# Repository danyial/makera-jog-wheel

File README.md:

# Makera jog wheel

A battery-powered Wi-Fi handwheel (MPG, manual pulse generator) for the **Makera Z1 Pro** desktop CNC mill. An ESP32 (DFRobot **FireBeetle 2 ESP32-UE**) with a 100-pulse handwheel, four axis buttons and a 1.3″ OLED connects directly to the machine over Wi-Fi and jogs X, Y, Z and optionally the rotary axis A. No PC needed, and it works alongside Makera Studio.

> **Safety first. Read the [safety notice](#safety) before you connect this to a machine.**

The firmware's user-facing texts (display, web UI, serial output) are in German; all documentation is in English.

## Features

- **Jog gate.** The machine only moves when an axis is selected, a fresh machine status is available and the machine is ready. A running job, an alarm, a stale status or lost Wi-Fi lock the wheel; motion by another client ends the jog session ([SPEC 8.5](SPEC.md), [8.7](SPEC.md)).
- **Bounded overrun.** Commands are planned inside a small window ahead of the machine position. When the wheel stops, the machine stops after at most that window (5 mm X/Y, 1 mm Z, 2° A); surplus detents are dropped, never queued ([SPEC 8.7](SPEC.md)).
- **Speed-dependent step size.** Slow turning moves 0.01 mm per detent, faster turning 0.05 and 0.1 mm, no range switch. The feed rate follows the turning speed and is capped by the machine's own maximum rates, read at runtime ([SPEC 8.6](SPEC.md)).
- **Axis selection** with lit buttons, auto-deselect after inactivity, and an optional rotary axis A.
- **Unlock after an alarm** by holding an axis button for 5 s (sends `$X`, like the unlock dialog in Makera Studio). Nothing moves afterwards without new turning ([SPEC 8.10](SPEC.md)).
- **Setup portal.** First start (or X held at power-on) opens an access point with a captive portal for Wi-Fi credentials, machine IP and options. No code changes needed.
- **Web UI** in normal operation (`http://handrad.local/`): read-only status page with machine state, position and battery, a 2D position map of the spoilboard and a 3D view (three.js, served from the handwheel's flash, no internet needed); password-protected settings page.
- **OTA updates** over Wi-Fi (espota), opt-in, password-protected, refused while an axis is selected or the battery is low ([SPEC 9.5](SPEC.md)).
- **Soft power.** The on/off button is an input; off means deep sleep, so the battery keeps charging over USB-C while the handwheel is off ([SPEC 9.3](SPEC.md)).
- **Battery monitoring**, low-battery warning and an orderly shutdown when empty; screensaver against OLED burn-in.
- **Tested core logic.** Everything that decides about motion lives in `lib/core` (plain C++17, no Arduino) and is covered by Unity tests that run on the host.

## Hardware

- **Bill of materials:** [`hardware/BOM.md`](hardware/BOM.md) (FireBeetle 2 ESP32-UE, ZSS600 handwheel, SH1106 OLED, 12 mm LED push buttons, 1S LiPo, u.FL antenna, connectors, screws).
- **Carrier board:** single-sided, millable 78 × 66 mm board, generated with KiCad's Python API. Gerber, drill and SVG/PDF files: [`hardware/README.md`](hardware/README.md), [`hardware/handrad_pcb/fab/`](hardware/handrad_pcb/fab/).
- **Enclosure:** printable two-part handheld enclosure (92 × 200 × 40 mm), STL and STEP: [`hardware/enclosure/README.md`](hardware/enclosure/README.md).
- **Wiring and pin map:** [`WIRING.md`](WIRING.md), GPIOs in [`include/pins.h`](include/pins.h).
- **Bring-up checks:** [`HARDWARE_CHECKLIST.md`](HARDWARE_CHECKLIST.md) lists everything that can only be verified on real hardware. Work through it before trusting the handwheel with a machine.

## Build and flash

Requires [PlatformIO](https://platformio.org/).

```bash
pio test -e native                 # unit tests of the core logic on the host
pio run -e firebeetle              # build the firmware
pio run -e firebeetle -t upload    # flash over USB
pio device monitor                 # serial console, 115200 baud
```

Over Wi-Fi, once "Update über WLAN erlauben" (allow update over Wi-Fi) is enabled in the settings and no axis is selected; the password is the handwheel password shown during setup:

```bash
HANDRAD_OTA_PASS=<handwheel password> pio run -e firebeetle-ota -t upload
```

The generated web assets (`src/web_assets.h`) are rebuilt with `python3 -I tools/make_web_assets.py`. Setup, the portal and all screens are described in [`SPEC.md`](SPEC.md) chapters 9 and 10.

## Documentation

- [`SPEC.md`](SPEC.md): the full specification (architecture, machine protocol, jog logic, constants, tests, acceptance criteria).
- [`DECISIONS.md`](DECISIONS.md): every design decision with question, decision and rationale, including the accepted residual risks.
- [`WIRING.md`](WIRING.md): netlist, connectors, safety notes.
- [`HARDWARE_CHECKLIST.md`](HARDWARE_CHECKLIST.md): manual hardware checks.

Some documents mention files that exist only in the author's private working copy (third-party CAD models, the Makera logo). They are not part of this repository; the firmware, board and enclosure build without them.

## Safety

This is a hobby project, provided **as is, without any warranty** (see [`LICENSE`](LICENSE)). It moves a real machine with a spinning tool.

- The handwheel **can move the machine**. A firmware bug, a hardware fault, a wrong pin map or a misread status can cause unexpected motion. Within the documented limits the machine may also keep moving for a short distance after the wheel stops.
- It is **not an emergency stop** and not a safety device. Keep the machine's own emergency stop within reach at all times.
- Test carefully: work through [`HARDWARE_CHECKLIST.md`](HARDWARE_CHECKLIST.md), start without a tool and with the spindle off, at a safe height, with small steps, and read the residual risks in [`DECISIONS.md`](DECISIONS.md) and [`WIRING.md`](WIRING.md).
- You use it at your own risk and are responsible for your machine, your workpiece and yourself.

## Trademarks

Makera and Carvera are trademarks of Makera Inc. This project is not affiliated with, endorsed by or sponsored by Makera; the names are used only to describe which machine the handwheel works with. The Makera logo is not included (the screensaver and the enclosure engraving show a neutral "MPG").

The spoilboard and rotary-axis dimensions in `include/spoilboard_geometry.h` and `include/a_axis_geometry.h` were derived (simplified hole positions and bounding boxes) from Makera's public CAD files at [github.com/MakeraInc/CarveraProfiles](https://github.com/MakeraInc/CarveraProfiles). The CAD files themselves are not included; `tools/make_spoilboard_geometry.py` and `tools/make_a_axis_geometry.py` regenerate the headers from your own download.

## Licence and third-party components

This project is licensed under the [MIT licence](LICENSE).

Third-party components:

- **three.js** 0.160.0 and its `OrbitControls` (`web/vendor/`, embedded gzipped in `src/web_assets.h`): MIT licence, © three.js authors, see [`web/vendor/three-LICENSE`](web/vendor/three-LICENSE).
- **KiCad libraries:** the board file contains footprints from the KiCad standard libraries and references their 3D models (not included); the board renders in `hardware/handrad_pcb/fab/` show those models. The KiCad libraries are licensed under CC BY-SA 4.0 with an exception for designs and generated files that use them ([kicad.org/libraries/license](https://www.kicad.org/libraries/license/)).
- Fetched at build time by PlatformIO, not included: **U8g2** (BSD 2-clause), **Arduino-ESP32** and **ESP-IDF** (LGPL 2.1 / Apache 2.0), **Unity** test framework (MIT).

The simplified FireBeetle and pogo-pin models in `hardware/models/` are generated by `hardware/models/make_models.py` and are part of this project.

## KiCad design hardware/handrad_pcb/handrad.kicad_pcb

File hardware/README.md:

# Carrier board (tickets #20, #25, #49)

The enclosure (ticket #30) is described in [`enclosure/README.md`](enclosure/README.md). The full bill of materials is in [`BOM.md`](BOM.md).

Single-sided, millable board for the handwheel: FireBeetle 2 ESP32-UE in female headers, AO3401, 0805 resistors, JST-XH connectors. Rounded corners (r = 3 mm), **78 × 66 mm**, 4 × M3.

## Files

| File | Contents |
|---|---|
| `generate_board.py` | Generates the board via KiCad Python (`pcbnew`). Source of truth for parts, nets and tracks. |
| `export.sh` | Generates board, DRC report and fabrication data into `handrad_pcb/fab/`. |
| `handrad_pcb/handrad.kicad_pcb` | Board (open in KiCad 10). |
| `handrad_pcb/fab/handrad-B_Cu.gbr` | Copper layer (bottom), Gerber |
| `handrad_pcb/fab/handrad-Edge_Cuts.gbr` | Outline, Gerber: **one** closed polyline, corner arcs as a fine polygon. Generated by `outline_gerber.py`, because Makera Studio does not recognise the KiCad outline (separate segments with arcs) as a board outline. |
| `handrad_pcb/fab/handrad.drl` | Drill file, Excellon (mm): 1.0 mm for all pins, 0.8 mm for J1 (JST-PH) and the pogo pins, 3.2 mm mounting holes |
| `handrad_pcb/fab/handrad-B_Cu-mirrored.svg` | Copper side seen from below (mirrored), alternative to the Gerber |
| `handrad_pcb/fab/handrad-1to1.pdf` | 1:1 top view for the paper test |
| `handrad_pcb/fab/handrad.step` | 3D model of the assembly (board, FireBeetle, female headers, connectors, SMD, pogo pins) for CAD/enclosure. **Private repository only** (ticket #50): with `hardware/vendor/` present the file contains the licensed DFRobot model, which must not be redistributed, so the public export leaves it out. `export.sh` regenerates it on every run. |
| `handrad_pcb/fab/handrad-3d.png`, `handrad-3d-bottom.png` | Renderings |
| `handrad_pcb/fab/handrad-top.png` | Top view render with the connector labels (J-number, function, pin names) |
| `handrad_pcb/fab/handrad-top-labels.svg` | 2D top view: silkscreen over the copper (seen from above) and outline |
| `models/make_models.py` | Generates the simplified STEP models for the FireBeetle (`firebeetle2_esp32ue.step`) and the pogo pin P50-J1 (`pogo_p50_j1.step`) |

To change: adjust the parameters at the top of `generate_board.py` (e.g. `ROW`), then run `./hardware/export.sh`.

## Layout

- **Landscape (ticket #25):** The FireBeetle sits on top of the board rotated by 90°, the USB-C socket points left and protrudes 1.0 mm beyond the board edge. The former right pin row (VCC … D10, 14 pins) is now the top row, the former left one (RST … RX, 18 pins) the bottom row.
- **Connector rows (rev 2, ticket #49):** upper row (y = 43 mm): J4 display, J6 handwheel (left), J2 on/off button (right end, next to the button in the right enclosure wall). Lower row (y = 54 mm, next to the board edge towards the axis buttons): J9 X, J8 Y, J5 Z, J7 A from left to right, pin 1 at x = 22.0 / 35.5 / 49.0 / 62.5. Battery J1 sits directly above J2 at the right edge (pin 1 at x 66.0, y 31.5): battery and on/off cables both go to the right side of the enclosure, and the battery tracks just run further down the right edge. Left of J2 in the upper row is impossible (the lanes on the right come down there); in the rows the battery lines would have to cross those lanes. Why this way round: the buttons sit just below the board in the enclosure (shortest leads, same order X, Y, Z, A as the buttons); the display cable comes from above; the handwheel cable comes over the battery anyway and reaches the upper row past the button plugs.
- **Topology (crossing-free on one layer):**
  - Battery: `BAT−` (outer) and `BAT+` run from the pogo pins upwards, along the top edge to the right and down the right edge to J1 above J2. `BAT+` is not switched: the battery is always on the FireBeetle's "Li-ion" pads (soft power, SPEC 9.3). The on/off lane passes below J1 into J2.
  - 3V3 rail above the top row; the pull-ups R4/R5 stand vertically right above the pins of buttons Z/A (GPIO35/36, input only).
  - Display (top row pins 2–5) inwards, under the FireBeetle to the left and down the left edge, then right into J4 from above. Next to it on the inside, `ENC_PWR` runs from bottom row pin 6 under the FireBeetle to the left, past RST, and into R6/Q1 from the left.
  - Q1 sits mirrored on the bottom side; its pins there necessarily follow G, S, D clockwise. With D at the bottom, G is on the left and S on the right. That is why `ENC_PWR` must come from the left.
  - Handwheel J6 (0V, A, B, V+): A/B jog left from bottom pins 7/8 into J6 pins 2/3; `ENC_VCC` runs from Q1 below J6 to V+ (pin 4) with R1/R2 below pins 2/3; the wheel's 0V comes from FireBeetle bottom pin 4 (GND) from above (net `GND_ENC`).
  - Buttons X and Y: bottom pins 12/13 (X) and 15/16 (Y) straight down between J6 and J2, then left in the band between the rows into J9/J8 from above (the line from the leftmost pin runs highest).
  - Right group: top pins 6, 7, 10, 11, 12 fan out under the FireBeetle (rightmost pin highest) into lanes right of the rows, inner to outer: LED_Z, BTN_Z, BTN_A, LED_A, PWR_SW. LED_Z/BTN_Z drop into J5 with a 45° jog, BTN_A/LED_A turn right in the band into J7, PWR_SW (outermost) turns right above everything into J2.
  - GND: J4 GND straight down to the bus along the lower edge, the bus to J7 pin 4; J2's GND drops straight onto J7 pin 4; all other button GND pins join the bus from above. GND from the FireBeetle comes via top row pin 3 (display line), the wheel's via bottom pin 4.
- **Two 3V3 and two GND nets:** `+3V3` (top row pin 2: display, button pull-ups) and `+3V3_ENC` (bottom row pin 2: R6, source of Q1); `GND` (top row pin 3: display, buttons, on/off) and `GND_ENC` (bottom row pin 4: wheel 0V). On the FireBeetle they are the same rails. On one layer they cannot be joined without crossing the display lines. That is why they have separate names and the DRC reports no unconnected items.
- **Copper on the bottom only (B.Cu).** Female headers and JST-XH are inserted **from the top** and soldered underneath. The SMD parts (R1, R2, R4–R6, Q1) sit **underneath** on the copper side.
- Pads enlarged for an annular ring ≥ 0.4 mm (no plated through-holes when milling).
- Milling rules: tracks 0.8 mm (supply 1.0 mm), clearance ≥ 0.4 mm (between parallel tracks ≥ 0.5 mm). No vias, no jumpers. No 90° bends: every bend is made of two 45° chamfers (only T junctions stay right-angled).
- M3 mounting holes symmetric, 4.5 mm from each corner.
- The bottom side must be mirrored for milling. In Makera Studio, import the Gerber as bottom layer or use the mirrored SVG. Check the mirroring on a paper printout first.

## Parts

| Ref | Part | Nets |
|---|---|---|
| U1A / U1B | Female header 1×18 (bottom) / 1×14 (top), 2.54 mm (FireBeetle) | see `include/pins.h` |
| Q1 | AO3401 (SOT-23), above J4/J6 | G = ENC_PWR (GPIO18), S = 3V3_ENC, D = ENC_VCC |
| R6 | 100 kΩ 0805, above Q1 | Gate pull-up ENC_PWR → 3V3_ENC |
| R1, R2 | 10 kΩ 0805, vertical below J6 A / B | Pull-ups ENC_A / ENC_B → ENC_VCC (switched wheel supply) |
| R4, R5 | 10 kΩ 0805, vertical above top pins 7 / 10 | Pull-ups BTN_Z / BTN_A → 3V3 (there is no R3) |
| J1 | **JST-PH** 2-pin (2.0 mm), right edge directly above J2 | Battery directly with its PH2.0 plug: 1 (top) = +, 2 = − |
| J2 | XH 2-pin, upper row right end (pin 2 above J7 pin 4) | On/off button (soft power, ticket #49): 1 = `PWR_SW` (GPIO4, internal pull-up), 2 = GND. Only a signal, no battery current |
| P1 | Pogo pin P50-J1 (round head, barrel Ø 0.68 mm, 16 mm, 2.6 mm travel), 0.8 mm hole | Battery − → "Li-ion −" pad on the FireBeetle underside |
| P2 | Pogo pin P50-J1, 0.8 mm hole | Battery + (always connected since ticket #49) → "Li-ion +" pad on the FireBeetle underside |
| J4 | XH 4-pin, upper row left | Display: 3V3, GND, SCL, SDA |
| J6 | XH 4-pin, upper row, right of J4 | Handwheel: 0V, A (GPIO23), B (GPIO19), VCC (switched) |
| J9 | XH 4-pin, lower row 1st | Button X: GND, GND, contact (GPIO13), LED+ (GPIO14) |
| J8 | XH 4-pin, lower row 2nd | Button Y: GND, GND, contact (GPIO26), LED+ (GPIO25) |
| J5 | XH 4-pin, lower row 3rd | Button Z: GND, GND, LED+ (GPIO15), contact (GPIO35) |
| J7 | XH 4-pin, lower row 4th | Button A: contact (GPIO36), LED+ (GPIO12), GND, GND |

Pin 1 of every connector is on the left (top for J1). Connector name (J-number and function, 1.2 mm) and pin names (0.8 mm) are printed on the silkscreen: above the upper row, below the lower row (see `fab/handrad-top.png`). Pin orders differ between the button connectors; follow the labels. Pin orders: J9 and J8 are G, G, SIG, LED; J5 is G, G, LED, SIG; J7 is SIG, LED, G, G. J5 cannot match J8/J9: of the lanes on the right only GPIO15 and GPIO12 can drive an LED (GPIO35/36 are input-only), LED Z must therefore be the inner lane GPIO15, and the lanes land on the connector pins in their order. J7 cannot match either: its last pin must be GND, because J2's GND drops straight onto it (any other GND path would cross the A lines).

Every button connector has two GND pins: one for the second green lead (button contact), one for LED− (black).

**Display pin order:** J4 is 3V3, GND, SCL, SDA. Many SH1106 modules have GND, VCC, SCL, SDA. Wire the cable by the labels on the module, not pin for pin.

**Battery and switch:** J1 is a PH socket, J2 an XH socket. So the battery only fits into J1. The on/off button only switches a signal (soft power, SPEC 9.3): with the button off the handwheel sleeps (about 0.5 mA, H-5) and the battery charges on USB. For storage unplug J1. Without the button cable in J2 the handwheel reads "off" and sleeps.

**Battery to the FireBeetle via pogo pins (P1/P2):** Two spring contacts press from below onto the FireBeetle's "Li-ion +/−" pads. The cable to the PH2.0 socket is not needed. The FireBeetle's PH2.0 socket then stays **empty**, otherwise two sources are in parallel.
- **Mounting the P50-J1:** relaxed head ≈ gap + 1.3 mm (half the travel) above the board's top side. With a calculated 11 mm gap (female header 8.5 mm + pin header spacer 2.5 mm) that is **≈ 12.3 mm**. Hold the pin at height with a 12.3 mm gauge (block or stack of washers) and solder it underneath. About 2 mm then protrude below. Measure the gap first. Do not bend the barrel (0.68 mm); the round head presses point-wise onto the flat pad and scratches through oxide.
- Position: starting point "−" centred between RST and 3V3, "+" level with the top edge of the NC pad (measured). Since ticket #25 each pin sits 0.5 mm further out (`POGO_SPREAD`, user request), centre distance **3.81 mm**, centre unchanged. Across ≈ 2.4 mm from the former right, now top FireBeetle edge (estimated from a photo, the pads are ≈ 3.7 mm wide). Parameters `POGO_*` in `generate_board.py`.
- Coordinates (top view, origin top left, y downwards): P1 (−) x = 12.49, y = 9.70; P2 (+) x = 16.30, y = 9.70.
- **Fallback:** solder a cable to the FireBeetle's PH2.0 plug into P1/P2 instead of pogo pins (P1 = −, P2 = +).
- Before powering up for the first time, check with a multimeter: P2 to pad "+" and P1 to pad "−", then plug in the battery (since ticket #49 J1 is live at once, there is no switch in the battery lead). A short circuit or reverse polarity at the battery is dangerous.

## Known points

- **DRC:** no errors, no unconnected items. Three silkscreen warnings at J1 are cosmetic only: the PH socket's pads are enlarged for milling and cut into their own silkscreen.
- **Header row spacing:** `ROW = 22.5` mm according to the official DFRobot footprint DFR0654 (not 0.9″ = 22.86 mm). Pin 1 (RST) is 11.32 mm below the USB edge. Check against the printout before milling anyway (H-11).
- **Enclosure placeholders (ticket #49):** both connector rows (housings board y 40.7…57.4, below z 22) lie inside `P_JST_rows` of `hardware/enclosure` (board y 39…58, full width); J1 (courtyard board x 62.7…68.3, y 29.0…36.0, below z 22; enclosure x ≈ 66…72, y ≈ 41…48) is no longer inside `P_JST_J1J2` (enclosure x 66…73, y 19…29), which marks its old place. Nothing of the enclosure lies at the new place (FireBeetle and female headers end at enclosure x 63.9, display and its pegs from z 30 up, standoffs at x 77), and the battery cable leaves towards the right wall as before, about 2 cm shorter. The enclosure geometry needs no change; the placeholder should move to y 41…48 at the next enclosure run (not done here: the CAD tool was not available).
- **Antenna:** The u.FL cable leaves at the right end of the FireBeetle. Route the cable to the top right, not over the connectors.

## 3D model

`export.sh` generates `fab/handrad.step` with all parts. The file is in the private repository only (see above) because it embeds the vendor model.

**Original FireBeetle model:** If `hardware/vendor/DFR0654.step` is present (DFRobot/SnapMagic package "DFR0654.zip", unpacked into `hardware/vendor/`; sources and licences in `hardware/vendor/README.md`), `generate_board.py` also writes a temporary board copy `handrad_pcb/handrad_vendor.kicad_pcb` with this model, and `export.sh` exports `fab/handrad.step` from it and deletes it. `handrad.kicad_pcb` and the renders always use the simplified model, so they do not depend on the vendor folder (ticket #50). The folder is committed in the private repository only and left out of the public export (`tools/strip_private.py`): the SnapMagic licence allows use in your own boards, but not redistribution of the model files themselves. Without the folder `handrad.step` contains the simplified model. There are no library models for the FireBeetle and the pogo pins; `models/make_models.py` builds them from boxes (dimensions from photos and the datasheet, good for fit and enclosure planning, not dimensionally exact in every detail).
Heights: female header 8.5 mm + pin header spacer 2.5 mm → FireBeetle underside 11.0 mm above the carrier board, board 1.6 mm, radio module +3.2 mm, PH2.0 +4.5 mm. The pogo pins are shown compressed.

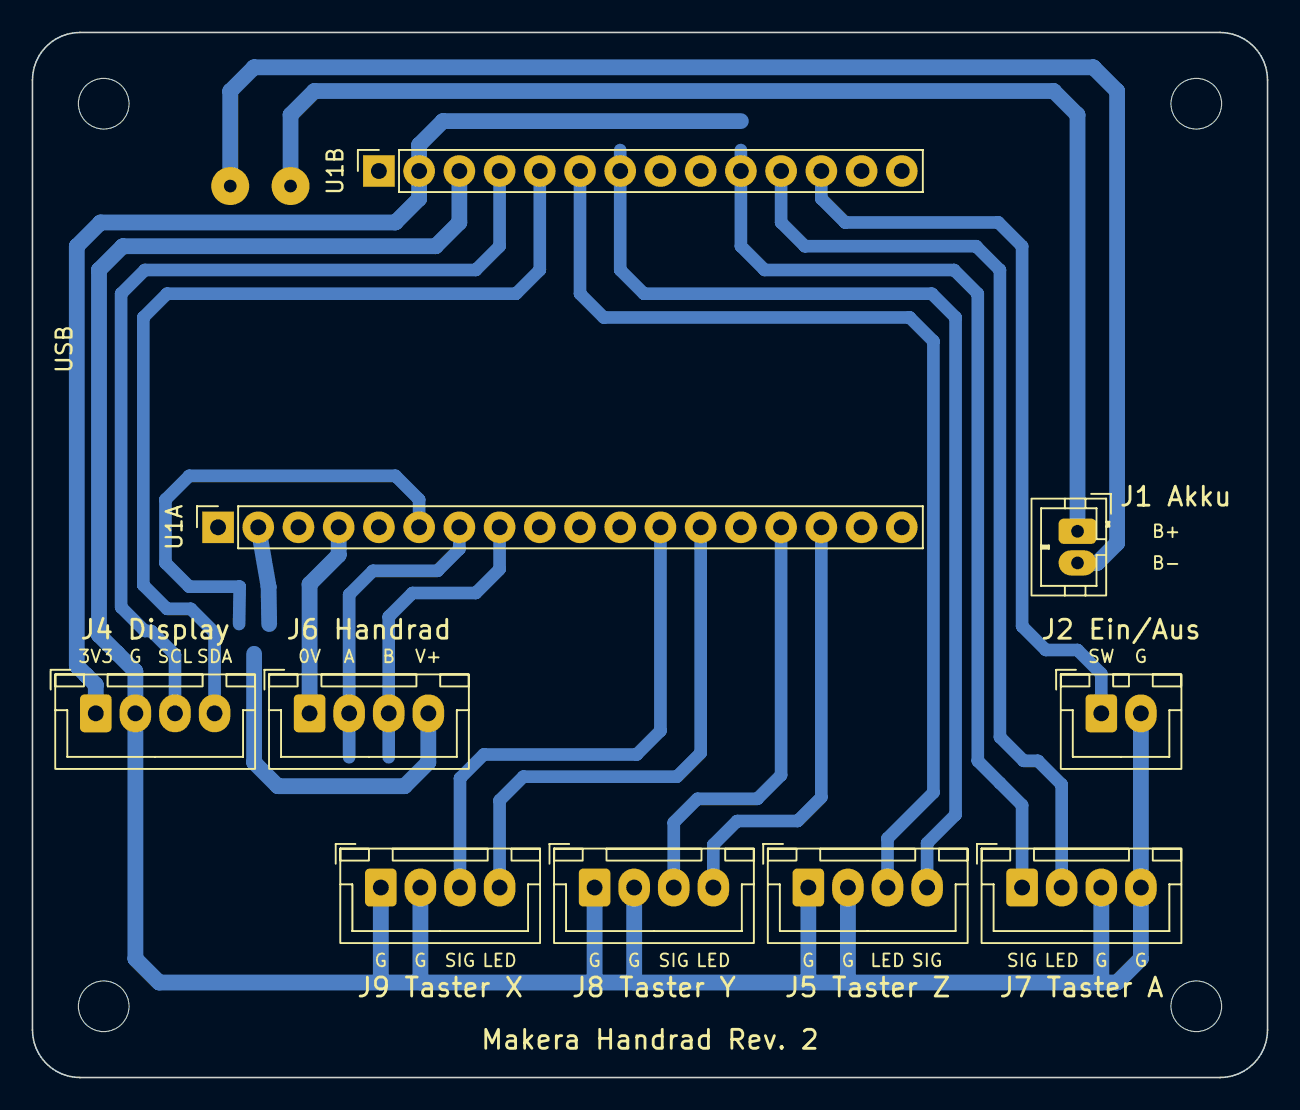
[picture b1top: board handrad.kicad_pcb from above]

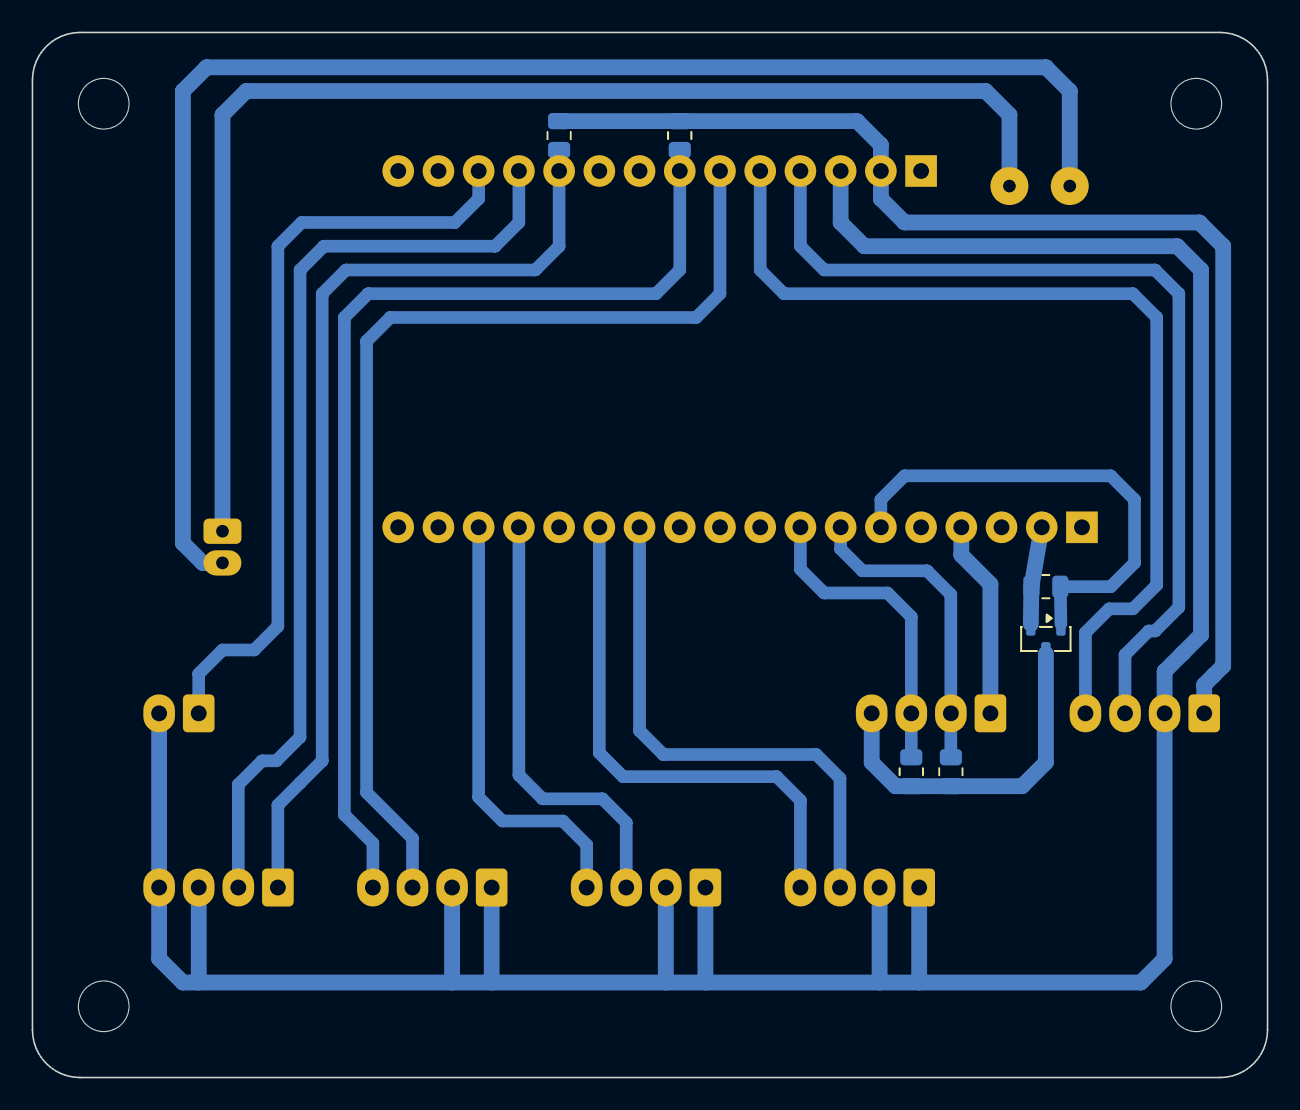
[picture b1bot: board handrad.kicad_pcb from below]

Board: 2 copper layers, 78.0 x 66.0 mm, 23 parts (6 on the bottom side), 21 nets.

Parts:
H1, H2, H3, H4: MountingHole_3.2mm_M3
J1: Akku PH2.0; JST_PH_B2B-PH-K_1x02_P2.00mm_Vertical
J2: Ein/Aus; JST_XH_B2B-XH-A_1x02_P2.50mm_Vertical
J4: Display; JST_XH_B4B-XH-A_1x04_P2.50mm_Vertical
J5: Taster Z; JST_XH_B4B-XH-A_1x04_P2.50mm_Vertical
J6: Handrad; JST_XH_B4B-XH-A_1x04_P2.50mm_Vertical
J7: Taster A; JST_XH_B4B-XH-A_1x04_P2.50mm_Vertical
J8: Taster Y; JST_XH_B4B-XH-A_1x04_P2.50mm_Vertical
J9: Taster X; JST_XH_B4B-XH-A_1x04_P2.50mm_Vertical
P1: Pogo BAT-
P2: Pogo BAT+
Q1: AO3401; SOT-23
R1, R2, R4, R5: 10k; R_0805_2012Metric
R6: 100k; R_0805_2012Metric
U1: FireBeetle 2 ESP32-UE
U1A: FireBeetle unten; PinSocket_1x18_P2.54mm_Vertical
U1B: FireBeetle oben; PinSocket_1x14_P2.54mm_Vertical

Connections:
+3V3: J4.1, R4.2, R5.2, U1B.2
+3V3_ENC: Q1.2, R6.1, U1A.2
BAT+: J1.1, P2.1
BAT-: J1.2, P1.1
BTN_A: J7.1, R5.1, U1B.10
BTN_X: J9.3, U1A.12
BTN_Y: J8.3, U1A.15
BTN_Z: J5.4, R4.1, U1B.7
ENC_A: J6.2, R1.2, U1A.7
ENC_B: J6.3, R2.2, U1A.8
ENC_PWR: Q1.1, R6.2, U1A.6
ENC_VCC: J6.4, Q1.3, R1.1, R2.1
GND: J2.2, J4.2, J5.1, J5.2, J7.3, J7.4, J8.1, J8.2, J9.1, J9.2, U1B.3
GND_ENC: J6.1, U1A.4
LED_A: J7.2, U1B.11
LED_X: J9.4, U1A.13
LED_Y: J8.4, U1A.16
LED_Z: J5.3, U1B.6
PWR_SW: J2.1, U1B.12
SCL: J4.3, U1B.4
SDA: J4.4, U1B.5

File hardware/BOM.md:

# Bill of Materials (ticket #43)

Everything needed for one handwheel. Sources: SPEC 7.1, `hardware/README.md` (carrier board), `hardware/enclosure/README.md` (enclosure). If anything conflicts, SPEC wins.

## Electronics

| Qty | Part | Details / notes | Ref |
|---|---|---|---|
| 1 | Microcontroller DFRobot **FireBeetle 2 ESP32-UE** (DFR1140) | ESP32-WROOM-32UE-N16R2, 16 MB flash, u.FL, LiPo charger, USB-C. With soldered pin headers 1 × 18 and 1 × 14 (2.54 mm) | U1 |
| 1 | Handwheel (MPG) **ZSS600-001-100B-5L** | 60 mm, 100 pulses/rev, 5 V, line driver; operated at 3.3 V (SPEC 7.2). Comes with its 3 M3 studs | J6 |
| 1 | Display **SH1106 1.3″** | 128 × 64, I2C, address 0x3C. Check the module's pin order (often GND, VCC, SCL, SDA) | J4 |
| 4 | 12 mm metal push button, **momentary**, green LED ring, IP65: Gebildet, pack of 4 ([Amazon B0HHJDQNP7](https://www.amazon.de/dp/B0HHJDQNP7)) | SPST 1 NO, 3 A, nickel-plated copper, pre-soldered leads. LED 3–9 V with built-in resistor, mounting nut M12; red = LED+, black = LED−, green/green = contact. X, Y, Z, A (A only with rotary axis) | J5, J7–J9 |
| 1 | 12 mm metal push button, **latching** (same series): Gebildet, pack of 4 ([Amazon B0HHJD2RKZ](https://www.amazon.de/dp/B0HHJD2RKZ)) | SPST 1 NO, self-locking, 3 A. On/off button, since ticket #49 only a **signal** (soft power, GPIO4 to GND, internal pull-up): no current from the battery flows through it, no extra parts (no resistor) needed. Only the contact is used (LED unconnected), 3 spare in the pack | J2 |
| 1 | Battery **YELUFT 3.7 V 3000 mAh LiPo 1S** with protection board ([Amazon B0F18QM8SJ](https://www.amazon.de/dp/B0F18QM8SJ)) | Protection at 3.0 V / 4.2 V, recommended charge current 0.6 A, 30 g. Ships with a **JST 1.25** plug; on the installed battery it was replaced with **JST-PH 2.0** because J1 is a PH socket. Polarity: J1 pin 1 (top) = +, pin 2 = −. Check with a multimeter before plugging in. Plug the battery into J1 only; it is then always connected to the FireBeetle (charges on USB even when switched off). The FireBeetle's own PH2.0 socket stays **empty**, otherwise two paths feed the board. For storage unplug J1 (the sleeping handwheel draws about 0.5 mA) | J1 |
| 1 | PCB adhesive antenna 2.4 GHz, 5 dBi, **u.FL**: sourcing map, pack of 2 ([Amazon B0816WKB5V](https://www.amazon.de/dp/B0816WKB5V)) | Board 50 × 15 mm, cable RF1.13 **195 mm**. Stuck inside the top end wall into the 51 × 16 × 0.3 mm positioning recess (centre x 46, z 25). Lay the surplus cable (~15 cm) as one loose flat loop on the free top edge of the carrier board, not over the antenna (`hardware/enclosure/README.md`) | — |

## Carrier board (single-sided, milled, `hardware/handrad_pcb`)

| Qty | Part | Details / notes | Ref |
|---|---|---|---|
| 1 | Single-sided copper-clad blank | at least 78 × 66 mm, 1.6 mm; copper on the bottom | — |
| 1 | Female header 1 × 18, 2.54 mm, 8.5 mm high | FireBeetle, bottom row | U1A |
| 1 | Female header 1 × 14, 2.54 mm, 8.5 mm high | FireBeetle, top row | U1B |
| 1 | P-channel MOSFET **AO3401** SOT-23, marking A19T: JXRSKJ, pack of 50 ([Amazon B0GXDJW88Q](https://www.amazon.de/dp/B0GXDJW88Q)) | Switches the handwheel supply (GPIO18); the pack also covers the conditional LED switches | Q1 |
| 4 | Resistor 10 kΩ 0805 | Pull-ups wheel A/B, buttons Z/A (X/Y use internal pull-ups) | R1, R2, R4, R5 |
| 1 | Resistor 100 kΩ 0805 | Gate pull-up Q1 | R6 |
| 2 | Pogo pin **P50-J1** ([Amazon B0988ZMG29](https://www.amazon.de/dp/B0988ZMG29), pack of 100, 3 A, 50 mΩ) | round head, barrel Ø 0.68, 16 mm, 2.6 mm travel; battery to the FireBeetle's "Li-ion +/−" pads | P1, P2 |
| 1 | **JST-PH** header 2-pin (2.0 mm), vertical | Battery | J1 |
| 1 | **JST-XH** header 2-pin (2.5 mm), vertical | On/off button (signal) | J2 |
| 6 | **JST-XH** header 4-pin (2.5 mm), vertical | Display, wheel, buttons X/Y/Z/A | J4–J9 |

## Cables and connectors

| Qty | Part | Notes |
|---|---|---|
| 1 | JST-XH housing 2-pin | On/off button |
| 6 | JST-XH housing 4-pin | Display, wheel, 4 buttons |
| approx. 30 | JST-XH crimp contacts | 26 needed, rest spare |
| 1 | JST-PH housing 2-pin + 2 crimp contacts | only if the battery plug still needs replacing |
| approx. 1 m | Stranded wire 0.14–0.25 mm² (AWG 26–24), several colours | Display, switch; buttons and wheel have their own leads |
| — | Heat-shrink tubing | Solder joints on buttons and wheel |

## Enclosure (`hardware/enclosure`)

| Qty | Part | Notes |
|---|---|---|
| 1 | Front shell `front_shell.stl` | PETG preferred (or PLA), 0.2 mm layers, 3 walls, 20 % gyroid |
| 1 | Bottom tray `bottom_tray.stl` | as above |
| 4 | Socket head cap screw M3 × 10 (ISO 4762) | Enclosure, from below |
| 4 | Heat-set insert M3, length ≤ 6 mm, for Ø 4.0 hole | Bosses of the front shell |
| 4 | Thread-forming screw M3 × 6 for plastic (or sheet-metal screw 2.9 × 6.5) | Carrier board |
| 3 | Nut M3 + washer | Handwheel studs at the bottom of the recess |
| approx. 20 cm | Hook-and-loop strap 16 mm | Battery |

## Conditional (only if a hardware check fails)

| Qty | Part | Needed when |
|---|---|---|
| 3 (4 with button A) | AO3401 SOT-23 + 100 kΩ 0805 each, high-side switch per button LED | H-3: LED current above 12 mA (SPEC 7.4) |
| 1 + 1 | 10 kΩ 0805 in series + 100 nF between gate and source of Q1 (soft start) | H-8: resets when switching on the wheel (SPEC 7.2) |
| 1 + 2 | 5 V step-up converter + BSS138 level shifter (A/B) | H-4: wheel loses steps at 3.3 V (SPEC 7.2) |

The battery voltage divider (H-6) is already on the FireBeetle (measured 2026-11-09, `DECISIONS.md`), so no extra parts are needed.

## Tools (not part of the build)

Milling machine for the board, 3D printer, soldering iron (also for the heat-set inserts), crimp tool for JST-XH/PH, multimeter, 12.3 mm gauge for the pogo pin height (`hardware/README.md`).

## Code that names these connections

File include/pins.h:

#pragma once
// GPIO assignment (SPEC 7.3). The ONLY place where GPIO numbers live.
// Mapping "silk label -> GPIO" must be confirmed on the device (HARDWARE_CHECKLIST H-1).
// Chosen so that the single-sided carrier PCB (hardware/) routes without crossings (tickets #21, #25, #49).
//
// Board revision (ticket #49): HANDRAD_BOARD_REV, evaluated only here and in src/ (lib/core is revision-free).
// 2 = soft power board: battery always connected, on/off button on GPIO4, own pin map (default without the flag).
#ifndef HANDRAD_BOARD_REV
#define HANDRAD_BOARD_REV 2
#endif
#if HANDRAD_BOARD_REV == 2
#define HANDRAD_BOARD_REV_VALID
#endif
#ifndef HANDRAD_BOARD_REV_VALID
#error "HANDRAD_BOARD_REV: unknown board revision"
#endif
constexpr int BOARD_REV = HANDRAD_BOARD_REV;

// Same on every board revision.
constexpr int PIN_ENC_A     = 23;  // MOSI handwheel A, 10k pull-up to switched wheel VCC
constexpr int PIN_ENC_B     = 19;  // MISO handwheel B, 10k pull-up to switched wheel VCC
constexpr int PIN_BAT_ADC   = 34;  // A2   on-board battery divider 1M/1M
constexpr int PIN_ENC_PWR   = 18;  // SCK  gate AO3401, 100k pull-up to 3V3; LOW = wheel on
constexpr int PIN_SDA       = 21;
constexpr int PIN_SCL       = 22;
constexpr int PIN_BOARD_BTN = 27;  // D4   on-board button, pressed = LOW

// Soft power board (ticket #49): buttons X, Y, Z, A in one connector row, display/wheel/on-off in the other.
constexpr int PIN_BTN_X     = 13;  // D7   internal pull-up, contact to GND
constexpr int PIN_BTN_Y     = 26;  // D3   internal pull-up, contact to GND
constexpr int PIN_BTN_Z     = 35;  // A3   10k pull-up to 3V3, contact to GND (input only)
constexpr int PIN_BTN_A     = 36;  // A0   rotary axis A button: 10k pull-up to 3V3, contact to GND (input only)
constexpr int PIN_LED_X     = 14;  // D6   LED+ of button X (GPIO14 outputs PWM briefly at boot: LED flickers)
constexpr int PIN_LED_Y     = 25;  // D2   LED+ of button Y
constexpr int PIN_LED_Z     = 15;  // A4   LED+ of button Z. Strapping MTDO: internal pull-up at reset against the
                                   //      LED to GND; either level is harmless (LOW only silences the ROM boot log)
constexpr int PIN_LED_A     = 12;  // D13  LED+ of button A. Strapping MTDI: must be LOW at reset (3.3 V flash); the
                                   //      LED to GND only pulls it down, never up
constexpr int PIN_PWR_SW    = 4;   // D12  on/off button (soft power): internal pull-up, contact to GND, closed = LOW
                                   //      = on; RTC GPIO, ext0 wake from deep sleep; no strapping pin
// GPIO39 (A1) stays unused on this board.

// Input-only GPIOs 34-39 have no internal pull-ups; their buttons have 10k pull-ups on the board.
constexpr bool pin_has_internal_pullup(int gpio) { return gpio < 34; }
